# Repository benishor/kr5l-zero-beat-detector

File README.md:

# kr5l-zero-beat-detector
KR5L CW Zero Beat Indicator

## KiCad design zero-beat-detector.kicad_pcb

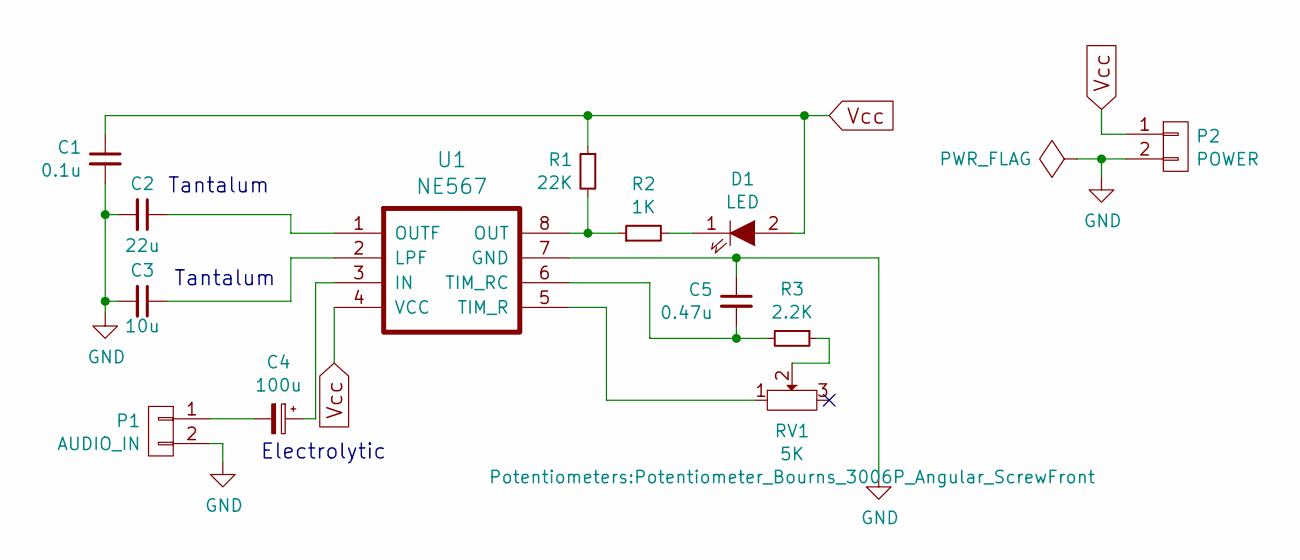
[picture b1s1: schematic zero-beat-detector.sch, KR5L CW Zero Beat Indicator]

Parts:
C1: 0.1u; C_Disc_D3_P2.5
C2: 22u; C_Disc_D3_P2.5
C3: 10u; C_Disc_D3_P2.5
C4: 100u; C_Radial_D7.5_L11.2_P2.5
C5: 0.47u; C_Rect_L7_W2.5_P5
D1: LED; LED-5MM
P1: AUDIO_IN; Pin_Header_Straight_1x02
P2: POWER; Pin_Header_Straight_1x02
R1: 22K; Resistor_Vertical_RM5mm
R2: 1K; Resistor_Vertical_RM5mm
R3: 2.2K; Resistor_Vertical_RM5mm
RV1: 5K; Potentiometer_Bourns_3006P_Angular_ScrewFront
U1: NE567; DIP-8_W7.62mm_LongPads

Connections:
GND: C1.2, C2.2, C3.2, C5.1, P1.2, P2.2, U1.7 (GND)
unnamed: C2.1, U1.1 (OUTF)
unnamed: C3.1, U1.2 (LPF)
unnamed: C4.1, U1.3 (IN)
unnamed: C4.2, P1.1
unnamed: C5.2, R3.2, U1.6 (TIM_RC)
unnamed: D1.1 (K), R2.2
unnamed: R1.2, R2.1, U1.8 (OUT)
unnamed: R3.1, RV1.2
unnamed: RV1.1, U1.5 (TIM_R)
Vcc: C1.1, D1.2 (A), P2.1, R1.1, U1.4 (VCC)

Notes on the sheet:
Tantalum
Electrolytic

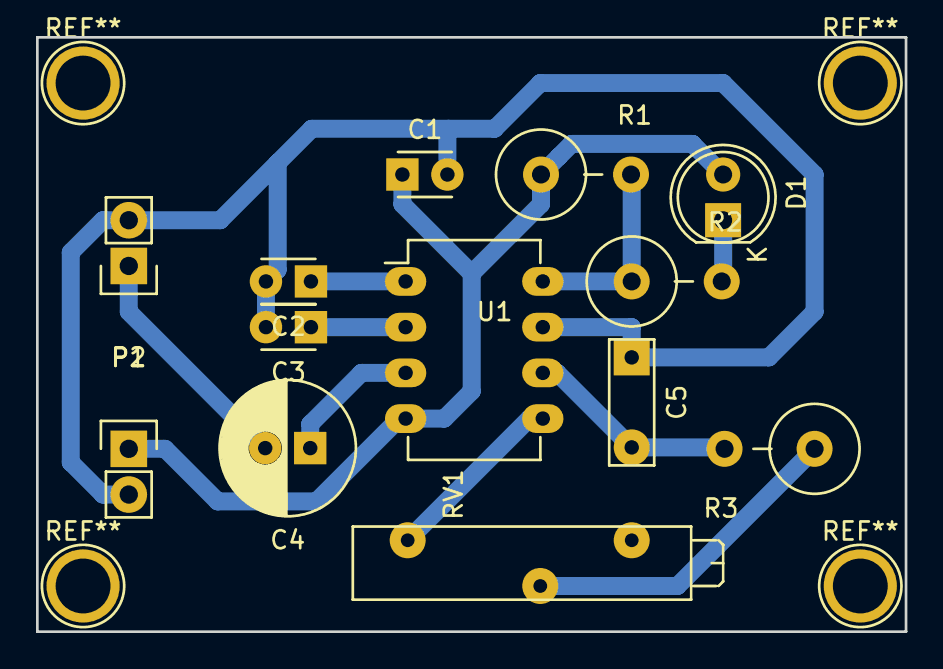
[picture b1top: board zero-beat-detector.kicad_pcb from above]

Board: 2 copper layers, 48.3 x 33.0 mm, 13 parts (0 on the bottom side), 11 nets.

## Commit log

2016-10-09 Initial import. Schematic captured and through-hole PCB available.
